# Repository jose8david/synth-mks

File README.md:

# synth-mks — DualSynth Poly

Teensy 4.1 polyphonic music synthesizer with USB/hardware MIDI input, I2S audio output via PCM5102A, and an ESP32 C3 Mini serving a WiFi web patch editor.

## Architecture

The project contains three firmware targets:

| Target | Board | Description |
|--------|-------|-------------|
| `src/main.cpp` | Teensy 4.1 | Original monophonic synth (2 detuned saws → SVF filter → envelope → I2S) |
| `src/MIDI/src/main.cpp` | Teensy 4.1 | Full polysynth — 4 voices, Moog Bass + Juno engines, effects, OLED UI |
| `src/ESP32/src/main.cpp` | ESP32 C3 Mini | WiFi Access Point with web-based patch editor and UART bridge to Teensy |

## Build

```bash
# Main Teensy firmware
pio run

# MIDI polysynth firmware
pio run -d src/MIDI

# ESP32 patch server
pio run -d src/ESP32
```

## Pin Connections

### PCM5102A I2S DAC → Teensy 4.1

| PCM5102A | Teensy 4.1 |
|----------|-------------|
| SCK      | GND (internal PLL, no master clock) |
| BCK      | Pin 21 (BCLK) |
| DIN      | Pin 7  (DOUT) |
| LRCK     | Pin 20 (LRCLK) |
| GND      | GND |
| VIN      | 3.3V |
| XSMT     | 3.3V (unmute) |
| FMT      | GND (I2S format) |

### EC11 Rotary Encoder → Teensy 4.1

| Encoder | Teensy 4.1 |
|---------|-------------|
| CLK     | Pin 2 |
| DT      | Pin 3 |
| SW (push) | Pin 4 (INPUT_PULLUP) |

### SH1106 OLED 128×64 (I2C) → Teensy 4.1

| OLED | Teensy 4.1 |
|------|-------------|
| SDA   | Pin 18 (Wire) |
| SCL   | Pin 19 (Wire) |
| VCC   | 3.3V |
| GND   | GND |

### Hardware MIDI (DIN-5) → Teensy 4.1

Uses `Serial1` with an external MIDI input circuit (optoisolator 6N138):

| MIDI DIN-5 | Teensy 4.1 |
|------------|-------------|
| Pin 4 (5V via 220Ω) | Pin 0 (RX1) via 6N138 |
| Pin 2 (GND) | GND |

See [`docs/MIDI.png`](docs/MIDI.png) for the circuit schematic.

### ESP32 C3 Mini ↔ Teensy 4.1 (UART)

Serial communication at 115200 baud for patch data exchange (JSON lines).

| ESP32 C3 Mini | Teensy 4.1 |
|---------------|-------------|
| GPIO20 (UART RX) | Pin 35 (TX8) |
| GPIO21 (UART TX) | Pin 34 (RX8) |
| GND | GND (common ground required) |

### Power

- USB-A female connector provides 5V input
- MP1584EN buck converter steps 5V down to 3.3V for the Teensy, ESP32, and peripherals

## MIDI CC Map (16 Potentiometers)

The polysynth (`src/MIDI`) maps the following MIDI CCs for external potentiometer control:

| Group | CC | Parameter | Range |
|-------|----|-----------|-------|
| **Filter** | 21 | Cutoff | 80–8000 Hz |
| | 22 | Resonance | 0.0–1.0 (Moog) / 0.7–5.0 (Juno) |
| | 23 | Envelope Amount | 0–6000 Hz |
| | 24 | Filter Decay | 50–2000 ms |
| **Envelope** | 25 | Attack | 1–2000 ms |
| | 26 | Decay | 10–2000 ms |
| | 27 | Sustain | 0.0–1.0 |
| | 28 | Release | 20–4000 ms |
| **Effects** | 91 | Reverb Mix | 0–100% |
| | 93 | Reverb Size | 0.0–1.0 |
| | 73 | Delay Time | 10–800 ms |
| | 70 | Delay Feedback | 0–85% |
| **LFO** | 71 | LFO Rate | 0.1–20 Hz |
| | 72 | LFO Depth | 0–100% |
| | 82 | LFO Destination | 0=filter, 1=pitch, 2=volume |
| | 83 | LFO Shape | 0=sine, 1=triangle, 2=sawtooth |
| **Mod Wheel** | 1 | Modulation Cutoff | 0–4000 Hz offset |

## ESP32 WiFi Patch Server

The ESP32 C3 Mini creates a WiFi Access Point:

- **SSID**: `SynthPatch`
- **Password**: `synthpatch`
- **Web UI**: `http://192.168.4.1`

Features:
- Edit all synth parameters via sliders
- 6 built-in presets (Minimoog Bass, Juno Pad, Moog Lead, Juno Strings, Acid Bass, Ambient Pad)
- Save/load user patches to LittleFS flash storage
- Send patches to the Teensy in real time over UART
- Periodic connection status ping (every 5 seconds)

## Upload

Compiled firmware is at:
- `.pio/build/teensy41/firmware.hex` (main/MIDI)
- `src/ESP32/.pio/build/esp32-c3-mini/firmware.bin` (ESP32)

Use [`teensy_loader_cli`](https://github.com/PaulStoffregen/teensy_loader_cli) for the Teensy:

```bash
teensy_loader_cli --mcu=TEENSY41 -w -v .pio/build/teensy41/firmware.hex
```

Use `pio run -d src/ESP32 --target upload` for the ESP32.

## PlatformIO Config Notes

- Main project uses `build_flags = -DUSB_MIDI_AUDIO_SERIAL` for USB MIDI + audio + serial
- MIDI subproject uses `-D USB_MIDI_SERIAL` for USB MIDI + serial
- ESP32 uses `board_build.filesystem = littlefs` for patch storage

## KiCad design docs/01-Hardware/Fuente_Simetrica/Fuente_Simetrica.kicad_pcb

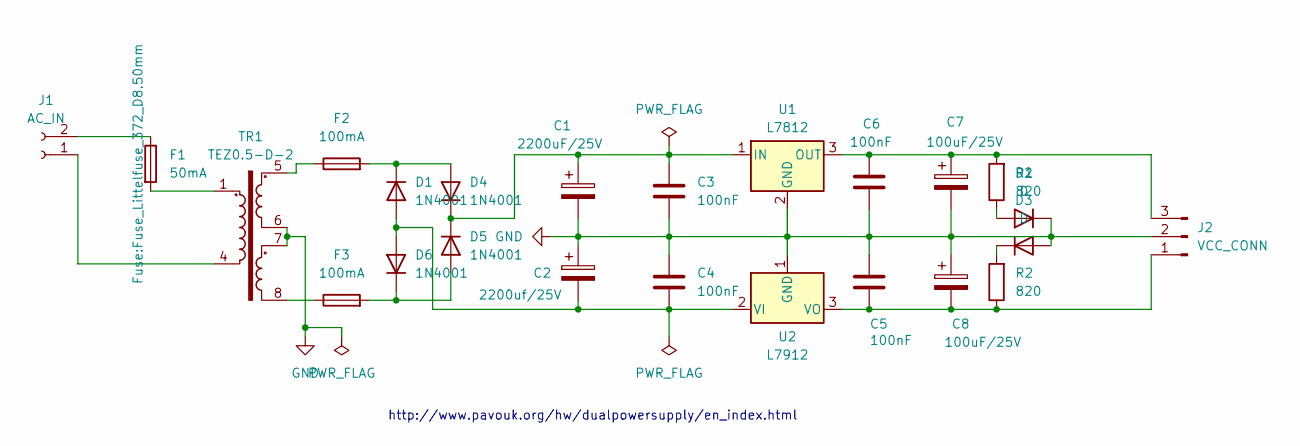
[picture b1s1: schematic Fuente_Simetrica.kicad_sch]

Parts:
C1: 2200uF/25V; CP_Radial_D16.0mm_P7.50mm
C2: 2200uf/25V; CP_Radial_D16.0mm_P7.50mm
C3, C4, C5, C6: 100nF; C_Disc_D5.0mm_W2.5mm_P2.50mm
C7, C8: 100uF/25V; CP_Radial_D8.0mm_P5.00mm
D1, D4, D5, D6: 1N4001; D_DO-41_SOD81_P10.16mm_Horizontal
D2, D3: D; LED_D3.0mm
F1: 50mA; Fuse_Littelfuse_372_D8.50mm
F2, F3: 100mA; Fuse_Littelfuse_372_D8.50mm
J1: AC_IN; JST_NV_B02P-NV_1x02_P5.00mm_Vertical
J2: VCC_CONN; JST_EH_B3B-EH-A_1x03_P2.50mm_Vertical
R1, R2: 820; R_Axial_DIN0207_L6.3mm_D2.5mm_P10.16mm_Horizontal
TR1: TEZ0.5-D-2; Transformer_Myrra_EI30-5_44000_Horizontal
U1: L7812; TO-220-3_Horizontal_TabDown
U2: L7912; TO-220-3_Horizontal_TabDown

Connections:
GND: C1.2, C2.1, C3.2, C4.1, C5.1, C6.2, C7.2, C8.1, D2.1 (K), D3.2 (A), J2.2, TR1.6, TR1.7, U1.2 (GND), U2.1 (GND)
unnamed: C2.2, C4.2, D1.2 (A), D6.2 (A), U2.2 (VI)
unnamed: D1.1 (K), D4.2 (A), F2.2
unnamed: D2.2 (A), R1.1
unnamed: D3.1 (K), R2.2
unnamed: C1.1, C3.1, D4.1 (K), D5.1 (K), U1.1 (IN)
unnamed: D5.2 (A), D6.1 (K), F3.2
unnamed: F1.2, TR1.1
unnamed: F2.1, TR1.5
unnamed: F3.1, TR1.8
unnamed: J1.1, TR1.4
unnamed: F1.1, J1.2
unnamed: C5.2, C8.2, J2.1, R2.1, U2.3 (VO)
unnamed: C6.1, C7.1, J2.3, R1.2, U1.3 (OUT)

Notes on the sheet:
http://www.pavouk.org/hw/dualpowersupply/en_index.html

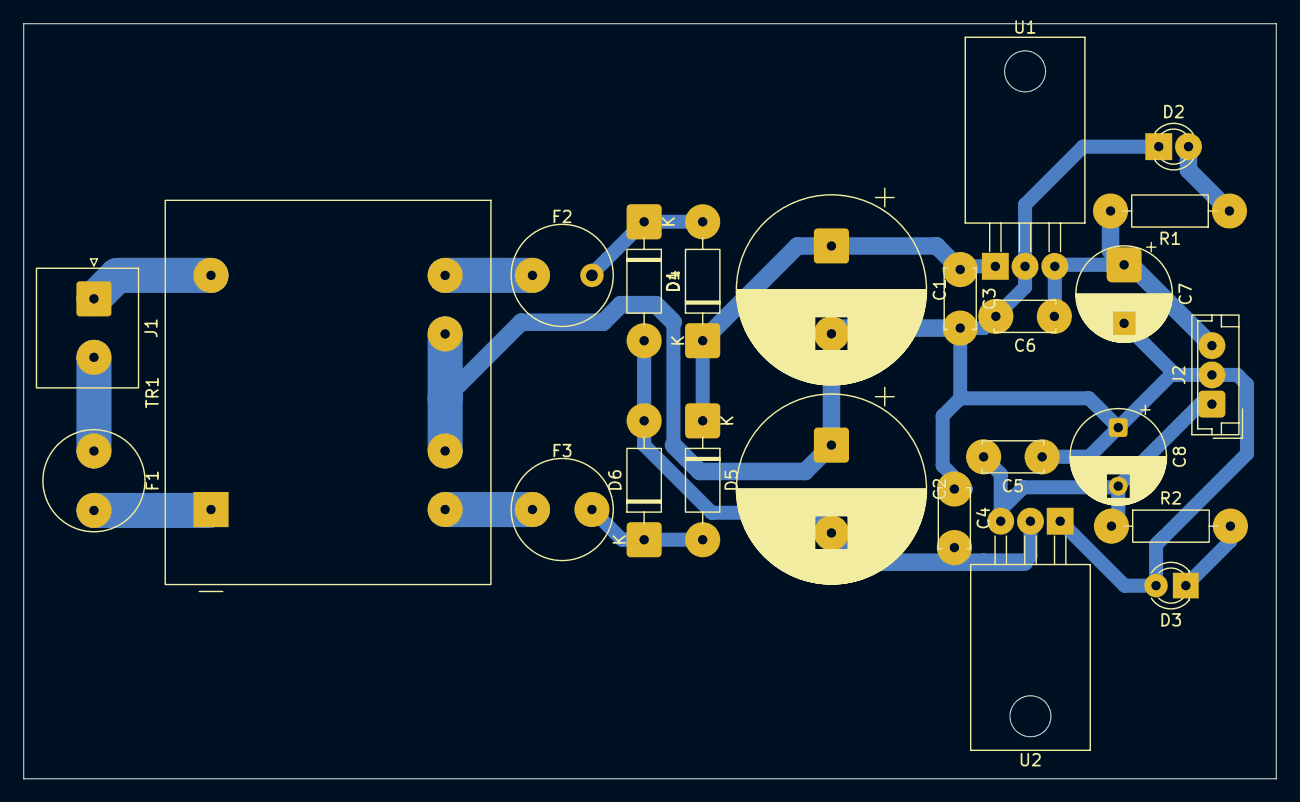
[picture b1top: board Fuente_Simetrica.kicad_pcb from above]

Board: 2 copper layers, 107.0 x 64.5 mm, 24 parts (0 on the bottom side), 14 nets.

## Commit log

2026-02-07 Initial commit: obsidian vault for mks synth project
2026-02-07 Remove .obsidian from repo, update .gitignore
2026-02-09 Add link to Teensy-based synthesizer project
    Added a link to an interesting project in IdeasIniciales.md.
2026-02-09 Add sections for complete projects and schematics
2026-02-10 Add components section to Fuente alimentación.md
2026-02-18 vault backup: 2026-02-18 21:30:22
2026-02-18 Dudas proyecto
2026-02-27 Update IdeasIniciales.md with new resources
    Added a link to a chord generator and updated notes on USB usage.
2026-03-03 Add section for power supply schematics
2026-03-03 Add purchasing information for Teensy 4.0 and 4.1
2026-04-03 vault backup: 2026-04-03 10:12:15
2026-04-03 jose8david: 2026-04-03 12:08:04
2026-04-03 jose8david: 2026-04-03 12:09:19
2026-04-07 jose8david 2026-4-7:16:0:17
2026-04-09 Últimos cambios PCB
2026-05-20 Move into docs
2026-05-20 Update version of git extension
2026-05-20 Base project from Platform IO
2026-05-22 Add dev container
2026-05-22 Fix devcontainer
2026-05-22 MIDI input and I2S output code
2026-05-22 Add devcontainer.lock
2026-05-22 Add usb build flag
2026-05-22 Add base CLAUDE.md
2026-05-22 Add readme
2026-05-22 All code
2026-06-06 MIDI
2026-06-28 Versión con configuración web y sonido JUNO y MOOG
2026-06-28 Versión documentada
